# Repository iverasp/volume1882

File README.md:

## Storing the wiper positions

The DS1882 has an internal EEPROM which can store the wiper positions. However, it will write to the EEPROM on all volume changes, which will quickly wear out the memory.

We therefore store the wiper positions in the Atmega328p EEPROM instead. This EEPROM is said to survive 100 000 writes. To avoid writing to the EEPROM on all volume changes, we wait until the user has let the rotary encoder untouched for 3 seconds.
At an estimate of 10 volume changes per day in average, this lets the EEPROM survive for at least 27 years.

## DS1882 address

A2, A1 and A0 on the DS1882 are tied to ground.
The address of the device therefore becomes 40 (00101000 in binary).

## BOM

All passive SMD parts are of package 1206

Electrolytic capacitors: 2x0.1uF + 1uF + 10uF. Designed for 5mm diameter (Nichicon KW/FG).  
SMD capacitors: 3x0.1uF ceramic  
SMD resistors: 560R, 120R, 240R, 1k1, 2x4k7, 3x10k, 3x470R  
Voltage regulators: LM337 and LM317, SOT-223 packages  
Diodes: 1N4002 through hole  
ICs: DS1882 SOIC16 and ATmega328p TQFP-32  
Male headers: 1pcs 1x5 pins, 2pcs 1x4 pins, 4pcs 1x3 pins, 1pcs 1x2 pins, 1pcs 2x3 pins

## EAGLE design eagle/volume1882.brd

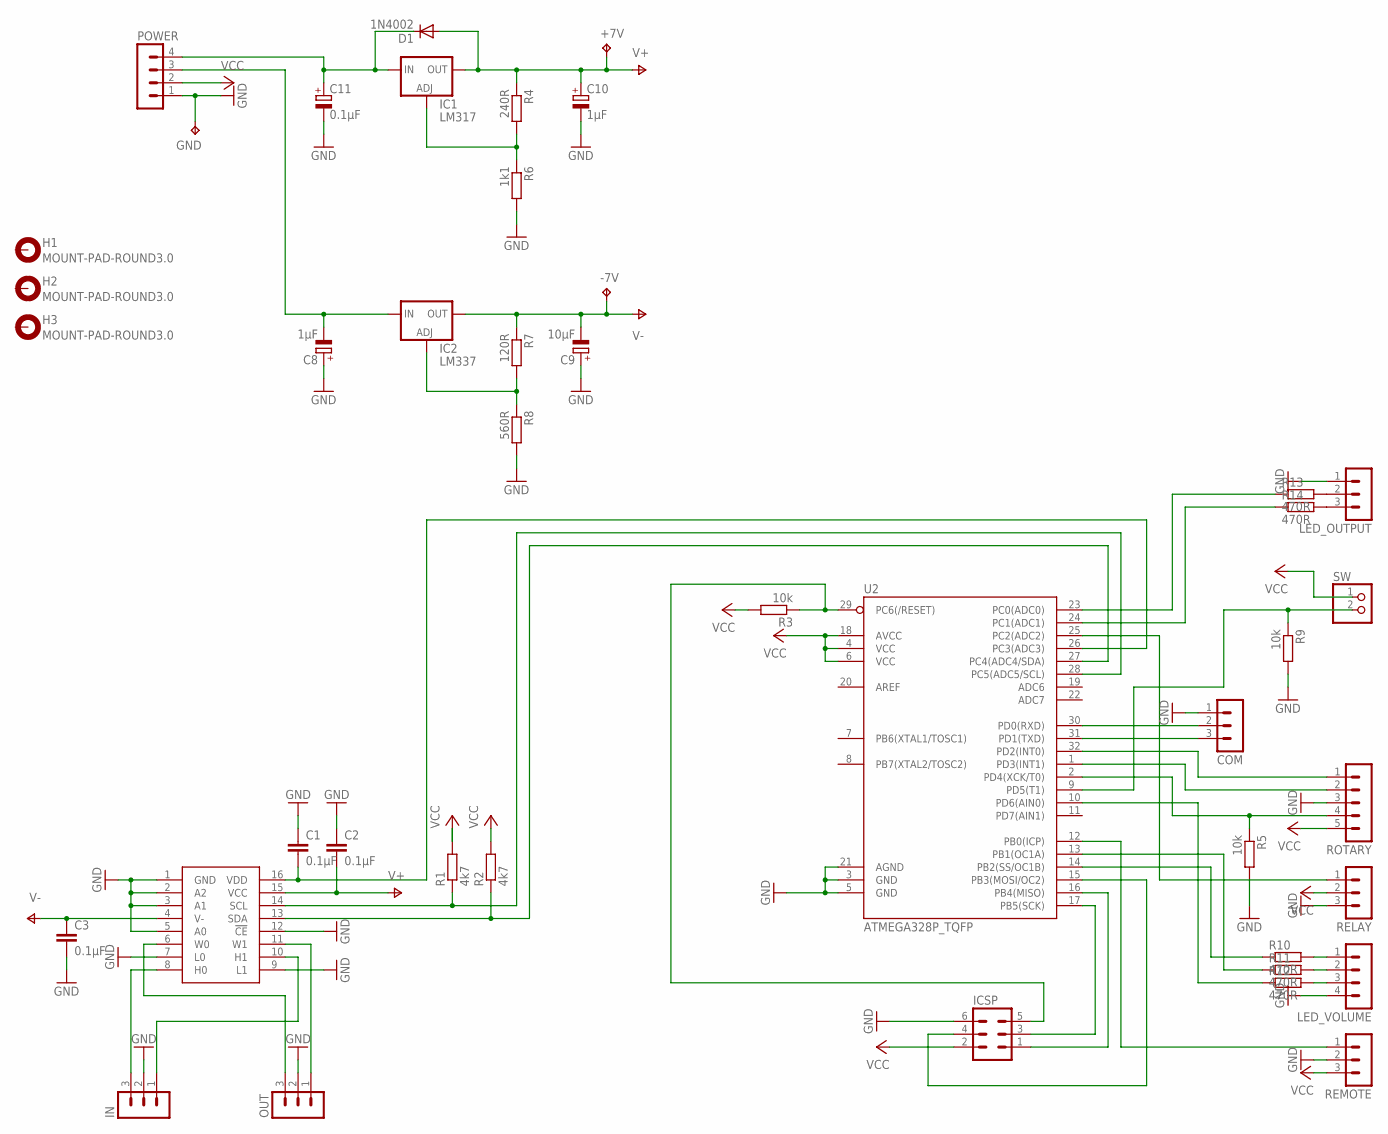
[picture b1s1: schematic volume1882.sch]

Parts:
+7V: TPTP12SQ; TP12SQ
-7V: TPTP12SQ; TP12SQ
C1, C2, C3: 0.1µF; C1206
C8, C10: 1µF; E2-5
C9: 10µF; E2-5
C11: 0.1µF; E2-5
COM: MA03-1
D1: 1N4002; DO41-10
GND: TPTP12SQ; TP12SQ
H1, H2, H3: MOUNT-PAD-ROUND3.0; 3,0-PAD
IC1: LM317; SOT223
IC2: LM337; SOT223
ICSP: MA03-2
IN: MA03-1
LED_OUTPUT: MA03-1
LED_VOLUME: MA04-1
OUT: MA03-1
POWER: MA04-1
R1, R2: 4k7; R1206
R3, R5, R9: 10k; R1206
R4: 240R; R1206
R6: 1k1; R1206
R7: 120R; R1206
R8: 560R; R1206
R10, R11, R12, R13, R14: 470R; R1206
RELAY: MA03-1
REMOTE: MA03-1
ROTARY: MA05-1
SW: PINHD-1X2; 1X02
U1: DS1882; SO16
U2: ATMEGA328P_TQFP; TQFP32-08

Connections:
GND: C1.1, C2.1, C3.2, C8.+, C9.+, C10.-, C11.-, COM.1, GND.TP, ICSP.6, IN.2, LED_OUTPUT.1, LED_VOLUME.4, OUT.2, POWER.1, R5.2, R6.2, R8.2, R9.2, RELAY.3, REMOTE.2, ROTARY.3, U1.1 (GND), U1.2 (A2), U1.3 (A1), U1.5 (A0), U1.7 (L0), U1.9 (L1), U1.12 (!CE), U2.3 (GND), U2.5 (GND), U2.21 (AGND)
unnamed: ICSP.5, R3.1, U2.29 (PC6(/RESET))
unnamed: ICSP.1, U2.16 (PB4(MISO))
unnamed: ICSP.3, U2.17 (PB5(SCK))
unnamed: ICSP.4, U2.15 (PB3(MOSI/OC2))
unnamed: R1.1, U1.14 (SCL), U2.28 (PC5(ADC5/SCL))
unnamed: R2.1, U1.13 (SDA), U2.27 (PC4(ADC4/SDA))
unnamed: COM.3, U2.31 (PD1(TXD))
unnamed: COM.2, U2.30 (PD0(RXD))
unnamed: ROTARY.1, U2.32 (PD2(INT0))
unnamed: ROTARY.2, U2.1 (PD3(INT1))
unnamed: R5.1, ROTARY.4, U2.2 (PD4(XCK/T0))
unnamed: C1.2, U1.16 (VDD), U2.26 (PC3(ADC3))
unnamed: R11.1, U2.13 (PB1(OC1A))
unnamed: R10.1, U2.14 (PB2(SS/OC1B))
unnamed: R12.1, U2.10 (PD6(AIN0))
unnamed: IN.3, U1.8 (H0)
unnamed: IN.1, U1.10 (H1)
unnamed: OUT.3, U1.6 (W0)
unnamed: OUT.1, U1.11 (W1)
unnamed: C11.+, D1.C, IC1.3 (IN), POWER.4
unnamed: C8.-, IC2.2 (IN), POWER.3
unnamed: IC1.1 (ADJ), R4.2, R6.1
unnamed: R9.1, SW.2, U2.9 (PD5(T1))
unnamed: IC2.1 (ADJ), R7.2, R8.1
unnamed: RELAY.1, U2.25 (PC2(ADC2))
unnamed: LED_VOLUME.1, R10.2
unnamed: LED_VOLUME.2, R11.2
unnamed: LED_VOLUME.3, R12.2
unnamed: R13.1, U2.23 (PC0(ADC0))
unnamed: R14.1, U2.24 (PC1(ADC1))
unnamed: LED_OUTPUT.2, R13.2
unnamed: LED_OUTPUT.3, R14.2
unnamed: REMOTE.1, U2.12 (PB0(ICP))
V+: +7V.TP, C2.2, C10.+, D1.A, IC1.4 (OUT), R4.1, U1.15 (VCC)
V-: -7V.TP, C3.1, C9.-, IC2.3 (OUT), R7.1, U1.4 (V-)
VCC: ICSP.2, POWER.2, R1.2, R2.2, R3.2, RELAY.2, REMOTE.3, ROTARY.5, SW.1, U2.4 (VCC), U2.6 (VCC), U2.18 (AVCC)

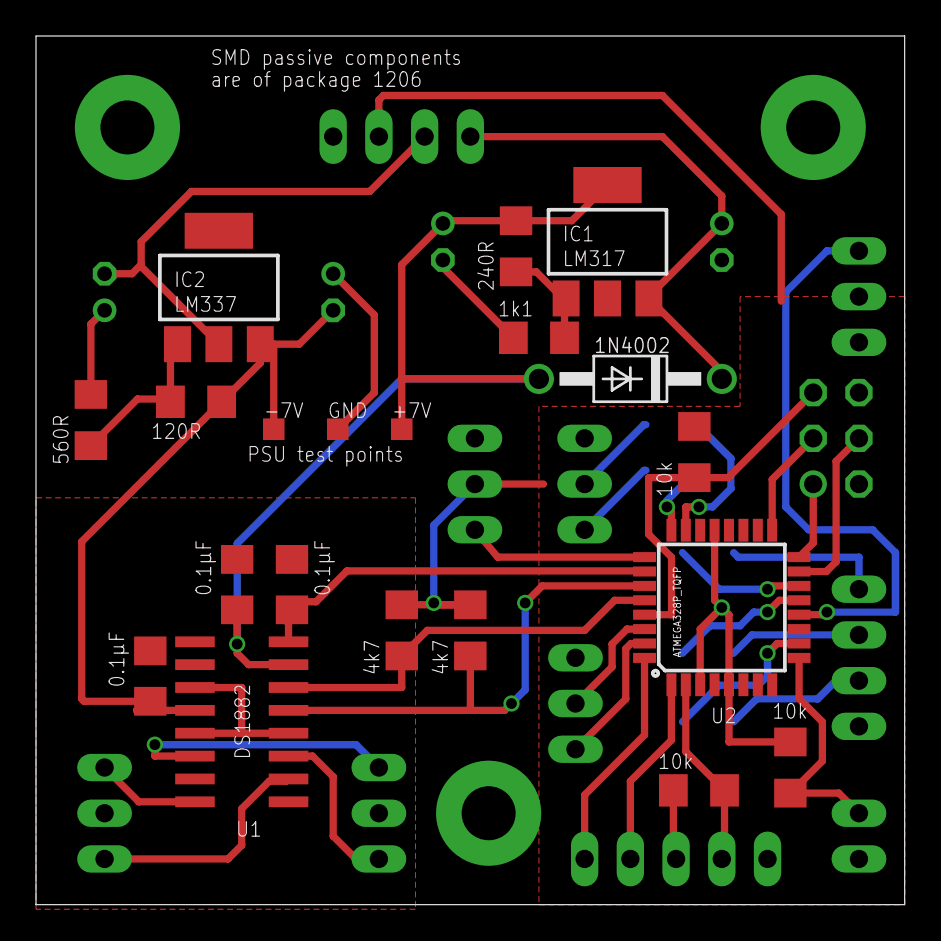
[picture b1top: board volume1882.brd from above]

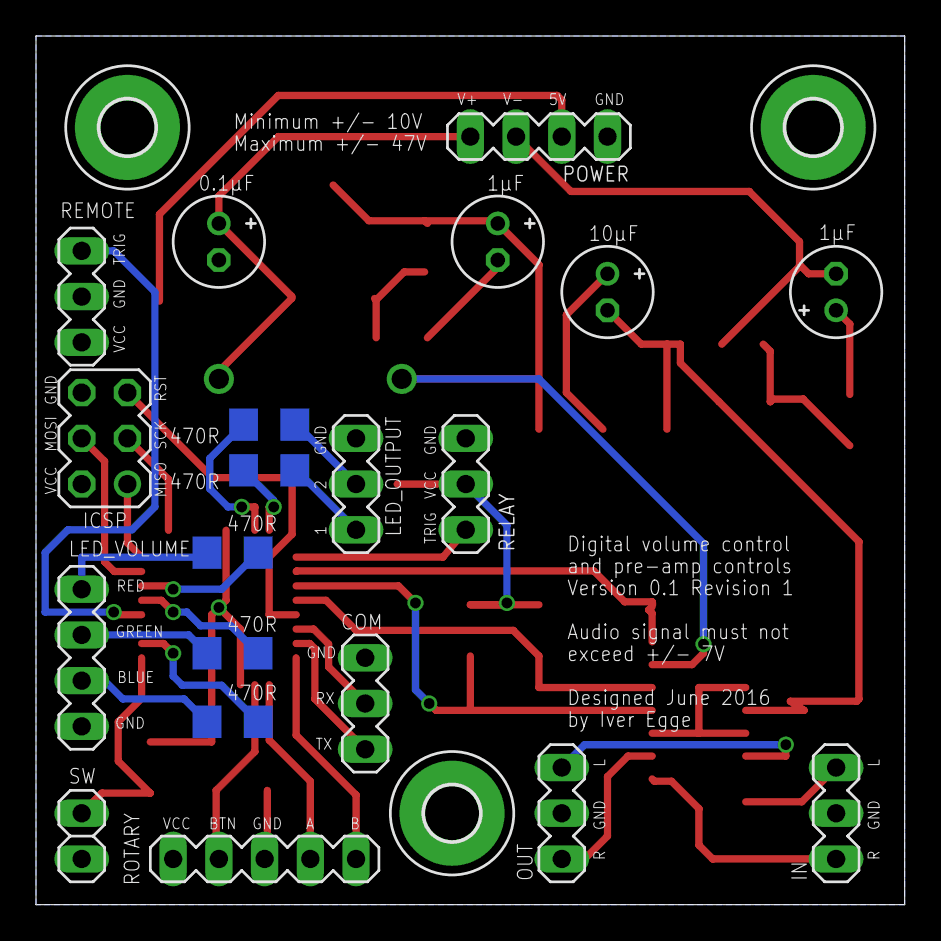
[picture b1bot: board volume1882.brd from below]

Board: 2 copper layers, 48.3 x 48.3 mm, 43 parts (23 on the bottom side), 37 nets.

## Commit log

2016-06-06 inital commit
2016-06-06 ardunino
2016-06-06 two settings for either poweramp or headphone amp
2016-06-12 eagle libraries for the ds1882 soic-16 and lm337 sot-223
2016-06-12 schematic
2016-06-12 output select switch
2016-06-13 finished board
2016-06-14 fixed wrong size parts
2016-06-16 small fixes

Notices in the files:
parts and their libraries:
SparkFun-DigitalIC: Licensing: Creative Commons ShareAlike 4.0 International - https://creativecommons.org/licenses/by-sa/4.0
